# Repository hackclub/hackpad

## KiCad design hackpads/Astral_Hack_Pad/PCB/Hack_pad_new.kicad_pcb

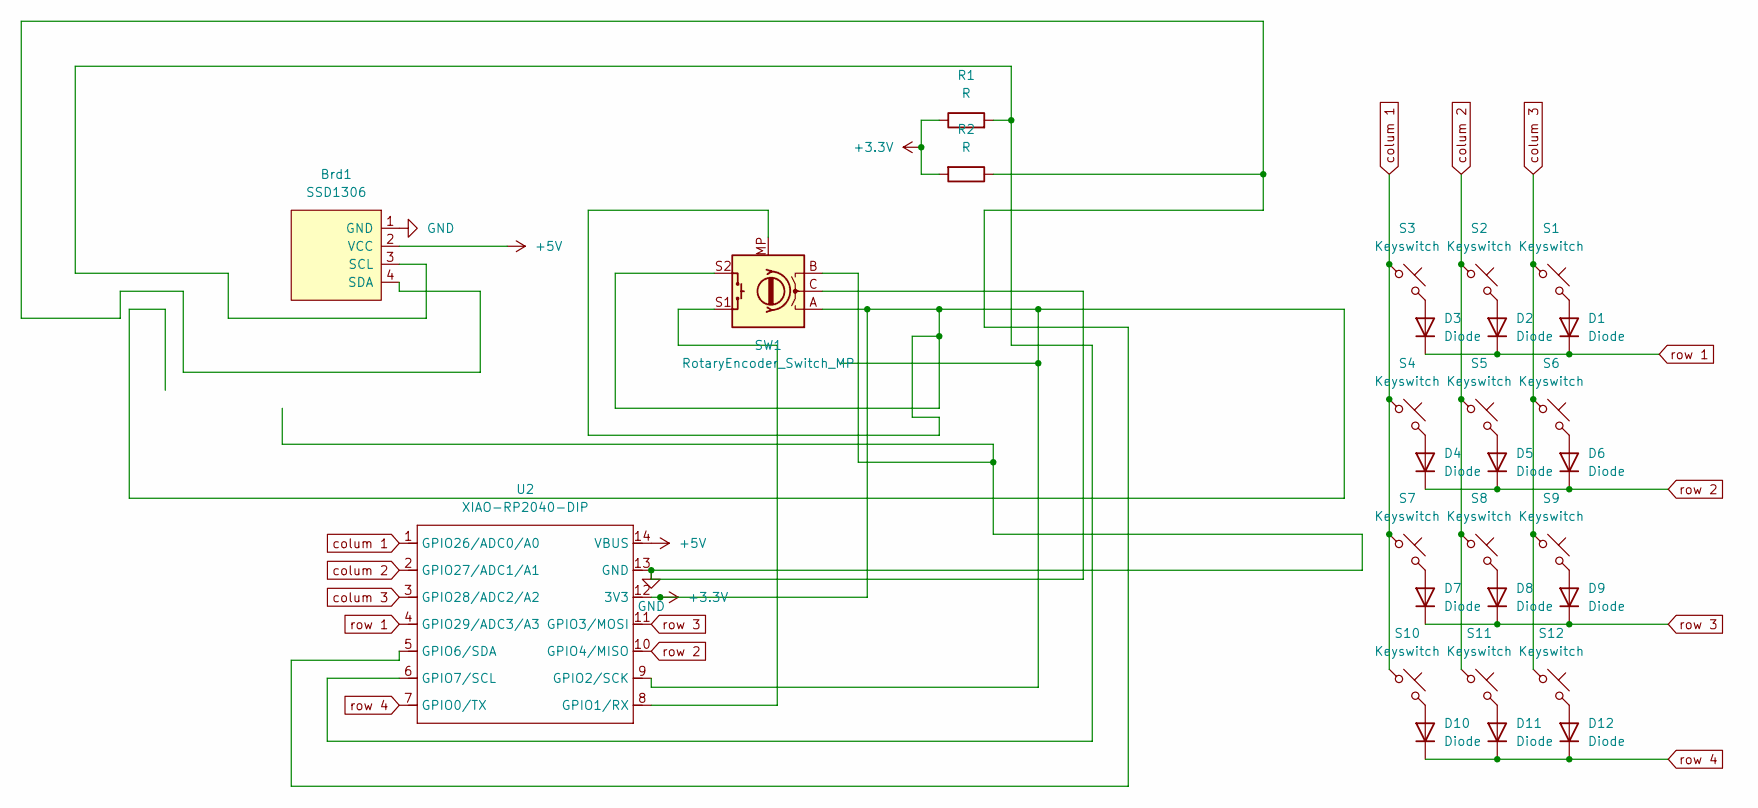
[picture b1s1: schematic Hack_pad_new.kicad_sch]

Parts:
Brd1: SSD1306; 128x64OLED
D1, D2, D3, D4, D5, D6, D7, D8, D9, D10, D11, D12: Diode; Diode_DO-35
R1, R2: R; R_Axial_DIN0204_L3.6mm_D1.6mm_P7.62mm_Horizontal
S1, S2, S3, S4, S5, S6, S7, S8, S9, S10, S11, S12: Keyswitch; MX_PCB_1.00u
SW1: RotaryEncoder_Switch_MP; Encoder_EC11_MX
U2: XIAO-RP2040-DIP

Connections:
+3.3V: R1.1, R2.2, SW1.A, SW1.MP, SW1.S2, U2.9 (GPIO2/SCK), U2.12 (3V3)
+5V: Brd1.2 (VCC), U2.14 (VBUS)
GND: Brd1.1 (GND), SW1.B, SW1.C, U2.13 (GND)
unnamed: Brd1.3 (SCL), R1.2, U2.6 (GPIO7/SCL)
unnamed: Brd1.4 (SDA), R2.1, U2.5 (GPIO6/SDA)
unnamed: D1.2 (A), S1.2
unnamed: D2.2 (A), S2.2
unnamed: D3.2 (A), S3.2
unnamed: D4.2 (A), S4.2
unnamed: D5.2 (A), S5.2
unnamed: D6.2 (A), S6.2
unnamed: D7.2 (A), S7.2
unnamed: D8.2 (A), S8.2
unnamed: D9.2 (A), S9.2
unnamed: D10.2 (A), S10.2
unnamed: D11.2 (A), S11.2
unnamed: D12.2 (A), S12.2
unnamed: SW1.S1, U2.8 (GPIO1/RX)
colum 1: S3.1, S4.1, S7.1, S10.1, U2.1 (GPIO26/ADC0/A0)
colum 2: S2.1, S5.1, S8.1, S11.1, U2.2 (GPIO27/ADC1/A1)
colum 3: S1.1, S6.1, S9.1, S12.1, U2.3 (GPIO28/ADC2/A2)
row 1: D1.1 (K), D2.1 (K), D3.1 (K), U2.4 (GPIO29/ADC3/A3)
row 2: D4.1 (K), D5.1 (K), D6.1 (K), U2.10 (GPIO4/MISO)
row 3: D7.1 (K), D8.1 (K), D9.1 (K), U2.11 (GPIO3/MOSI)
row 4: D10.1 (K), D11.1 (K), D12.1 (K), U2.7 (GPIO0/TX)

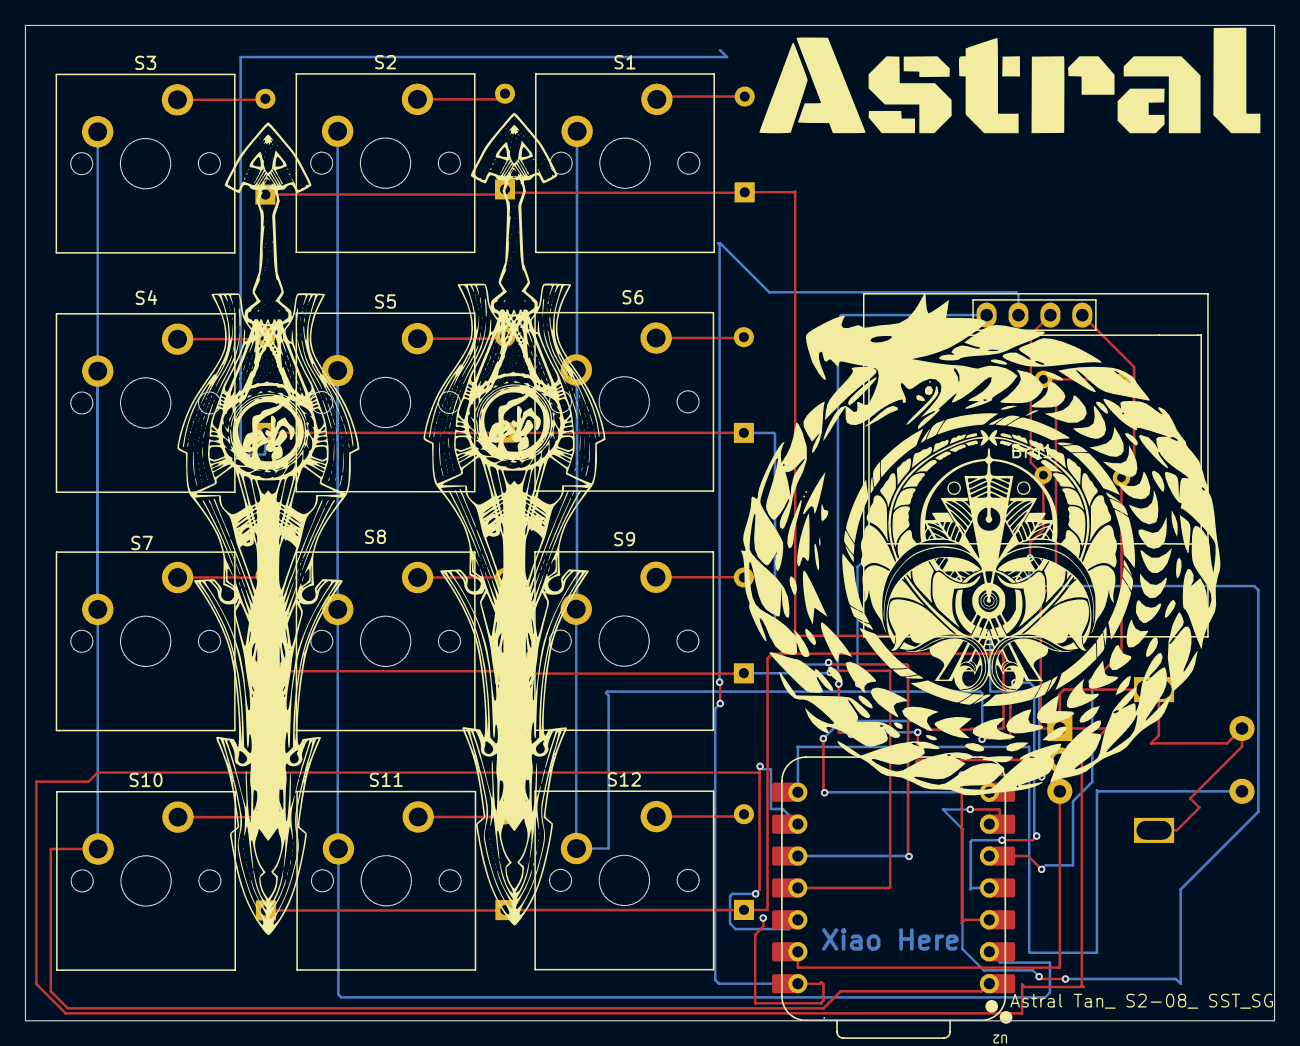
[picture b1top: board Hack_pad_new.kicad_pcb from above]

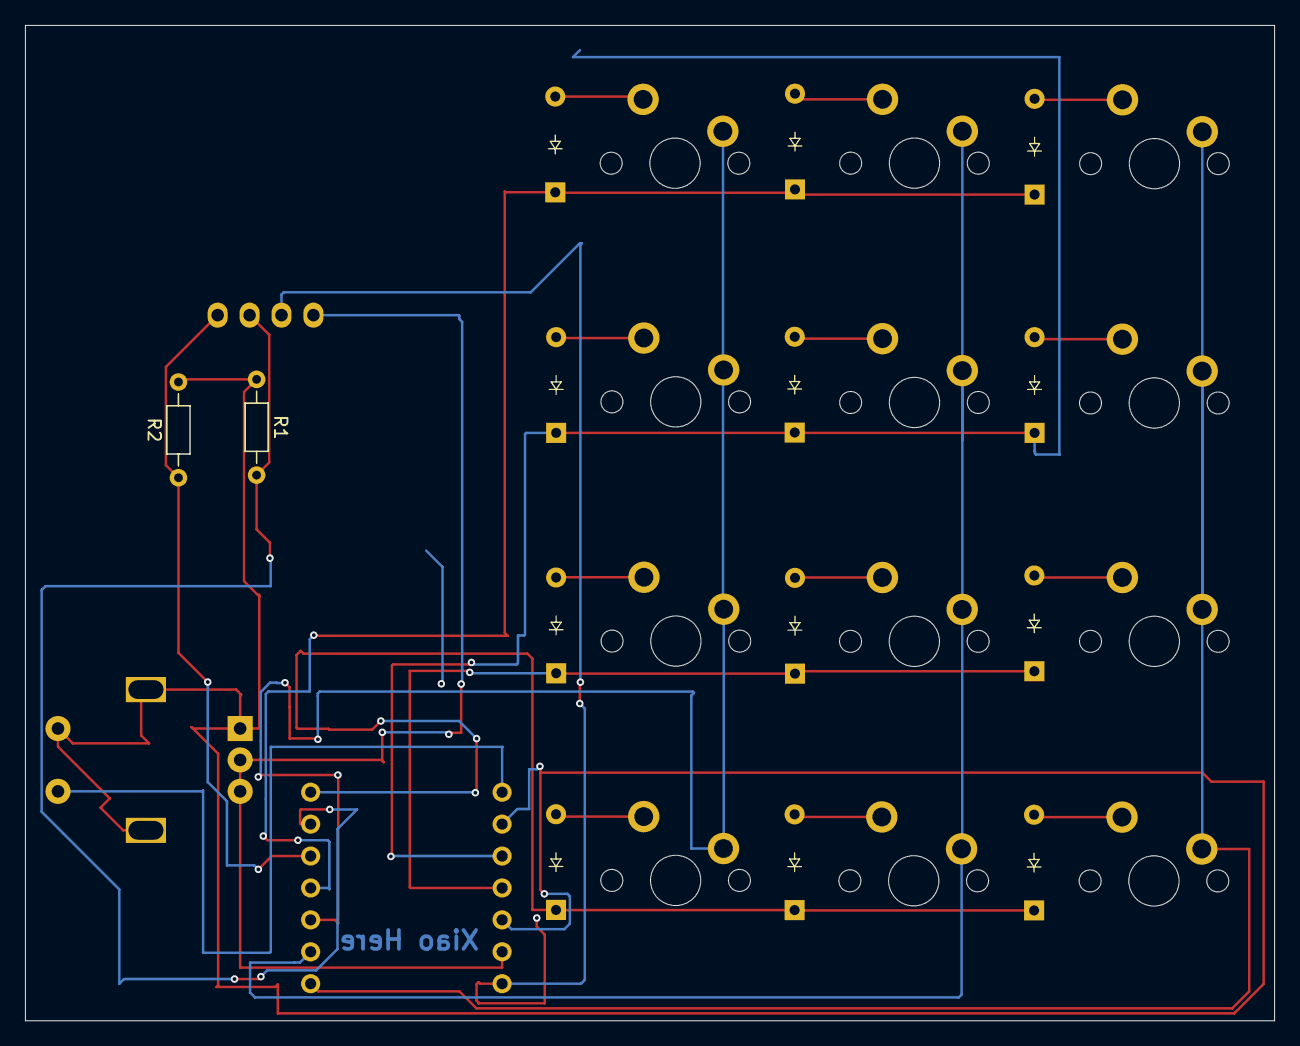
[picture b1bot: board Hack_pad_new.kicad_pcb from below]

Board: 2 copper layers, 99.4 x 79.2 mm, 29 parts (14 on the bottom side), 25 nets.

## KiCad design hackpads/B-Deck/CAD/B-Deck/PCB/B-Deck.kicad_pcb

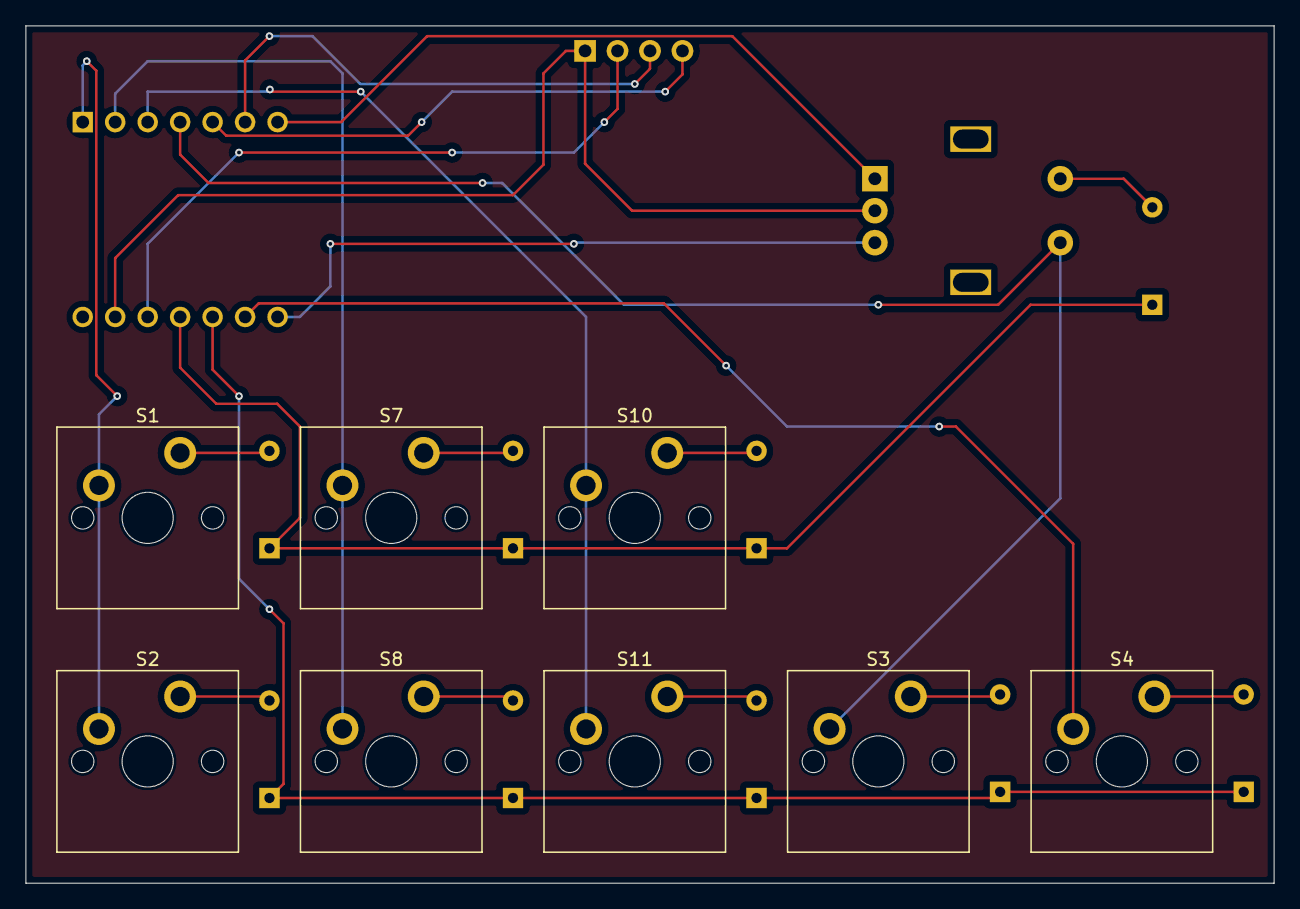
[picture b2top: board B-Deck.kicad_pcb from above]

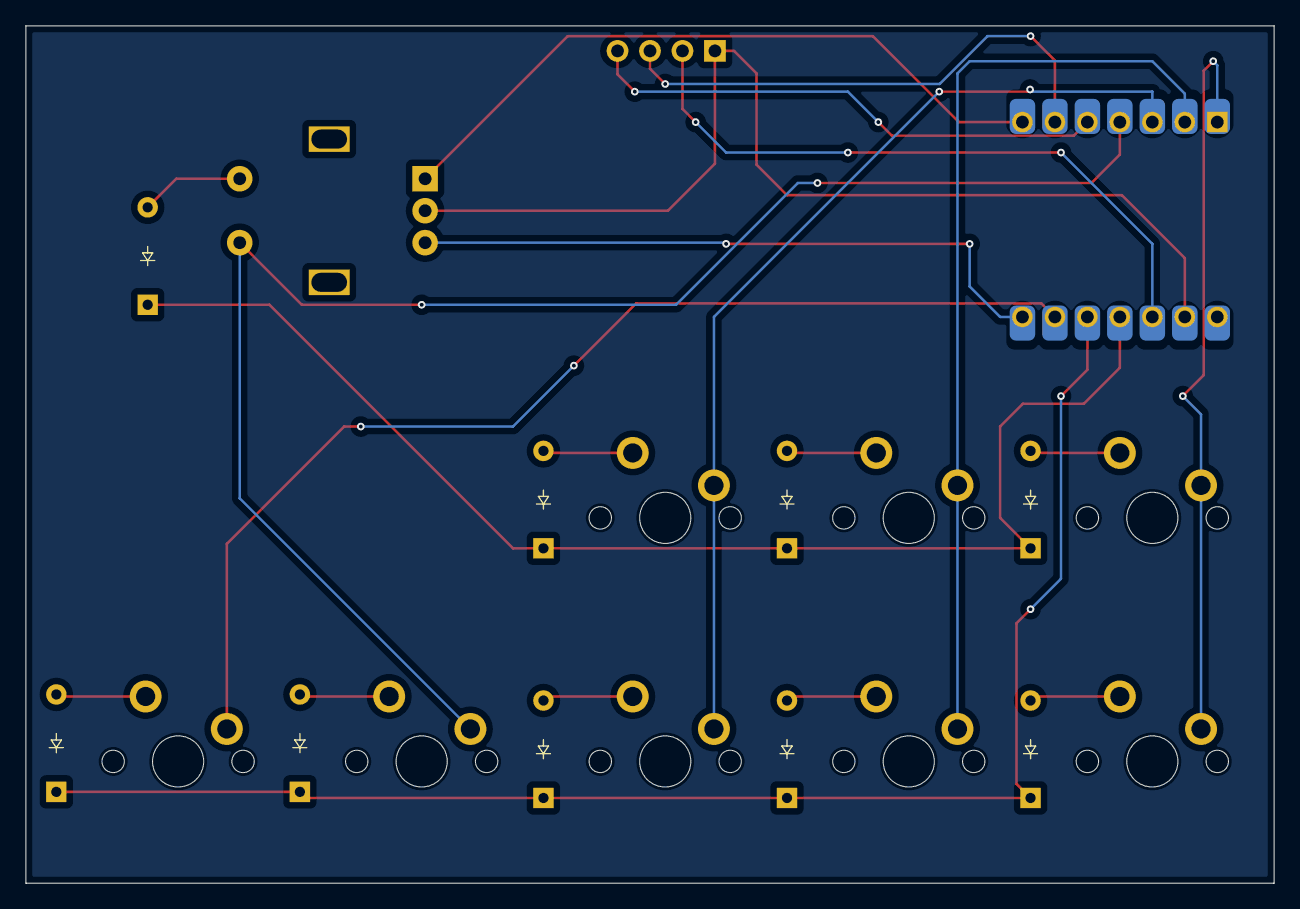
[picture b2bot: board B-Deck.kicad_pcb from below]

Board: 2 copper layers, 97.6 x 67.1 mm, 20 parts (10 on the bottom side), 22 nets.

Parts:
D1, D3, D4, D5, D6, D7, D8, D10, D11: Diode; Diode_DO-35
J1: OLED_128x64
S1, S2, S3, S4, S7, S8, S10, S11: Keyswitch; MX_PCB_1.00u
SW2: RotaryEncoder_Switch; Encoder_EC11_MX
U1: MCU_Seeed_XIAO_RP2040; Seeed_XIAO_RP2040

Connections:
Column 0: S1.1, S2.1, U1.1 (PA02_A0_D0)
Column 1: S7.1, S8.1, U1.2 (PA4_A1_D1)
Column 2: S10.1, S11.1, U1.3 (PA10_A2_D2)
Column 3: S3.1, SW2.S1, U1.4 (PA11_A3_D3)
Column 4: S4.1, U1.9 (PA7_A8_D8_SCK)
GND: J1.1 (GND), SW2.C, U1.13 (GND)
unnamed: D3.2 (A), S3.2
unnamed: D4.2 (A), S4.2
unnamed: D5.2 (A), S1.2
unnamed: D6.2 (A), S2.2
unnamed: D7.2 (A), S7.2
unnamed: D8.2 (A), S8.2
unnamed: D10.2 (A), S10.2
unnamed: D11.2 (A), S11.2
unnamed: J1.3 (SCL), U1.6 (PA9_A5_D5_SCL)
unnamed: J1.4 (SDA), U1.5 (PA8_A4_D4_SDA)
unnamed: J1.2 (VCC), U1.12 (3V3)
unnamed: SW2.A, U1.7 (PB08_A6_D6_TX)
unnamed: SW2.B, U1.8 (PB09_A7_D7_RX)
RE S2: D1.2 (A), SW2.S2
Row 0: D1.1 (K), D5.1 (K), D7.1 (K), D10.1 (K), U1.11 (PA6_A10_D10_MOSI)
Row 1: D3.1 (K), D4.1 (K), D6.1 (K), D8.1 (K), D11.1 (K), U1.10 (PA5_A9_D9_MISO)

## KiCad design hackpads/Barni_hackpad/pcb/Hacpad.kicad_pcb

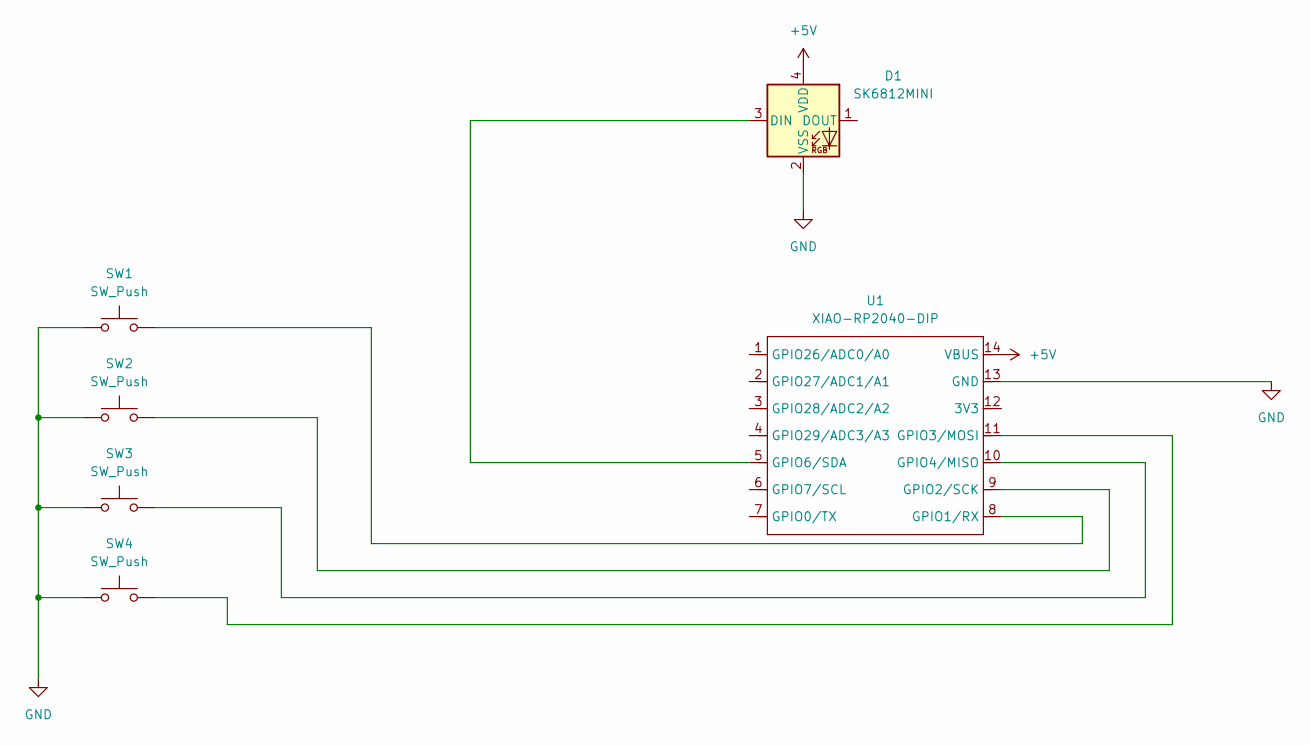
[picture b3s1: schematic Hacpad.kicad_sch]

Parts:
D1: SK6812MINI; LED_SK6812MINI_PLCC4_3.5x3.5mm_P1.75mm
SW1, SW2, SW3, SW4: SW_Push; SW_Cherry_MX_1.00u_PCB
U1: XIAO-RP2040-DIP

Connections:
+5V: D1.4 (VDD), U1.14 (VBUS)
GND: D1.2 (VSS), SW1.1, SW2.1, SW3.1, SW4.1, U1.13 (GND)
unnamed: D1.3 (DIN), U1.5 (GPIO6/SDA)
unnamed: SW1.2, U1.8 (GPIO1/RX)
unnamed: SW2.2, U1.9 (GPIO2/SCK)
unnamed: SW4.2, U1.11 (GPIO3/MOSI)
unnamed: SW3.2, U1.10 (GPIO4/MISO)

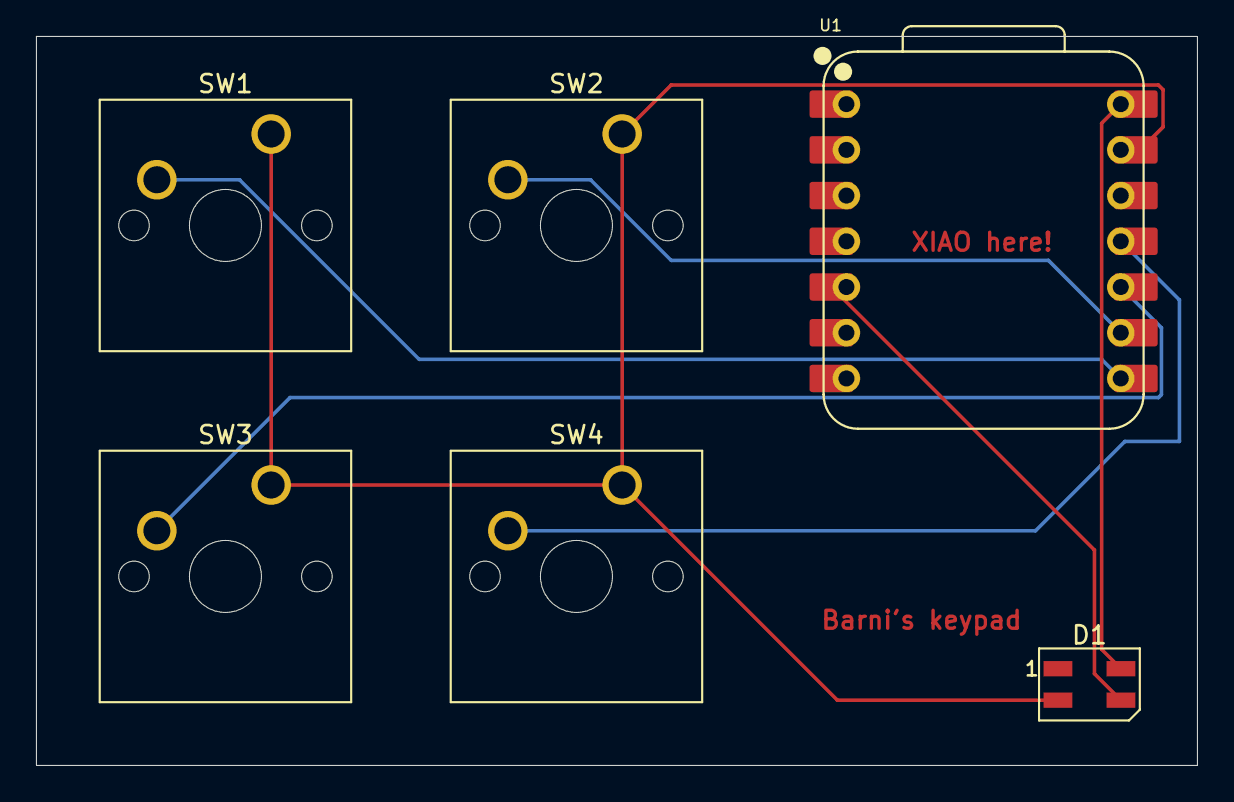
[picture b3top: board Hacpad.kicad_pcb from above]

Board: 2 copper layers, 64.5 x 40.5 mm, 6 parts (0 on the bottom side), 7 nets.

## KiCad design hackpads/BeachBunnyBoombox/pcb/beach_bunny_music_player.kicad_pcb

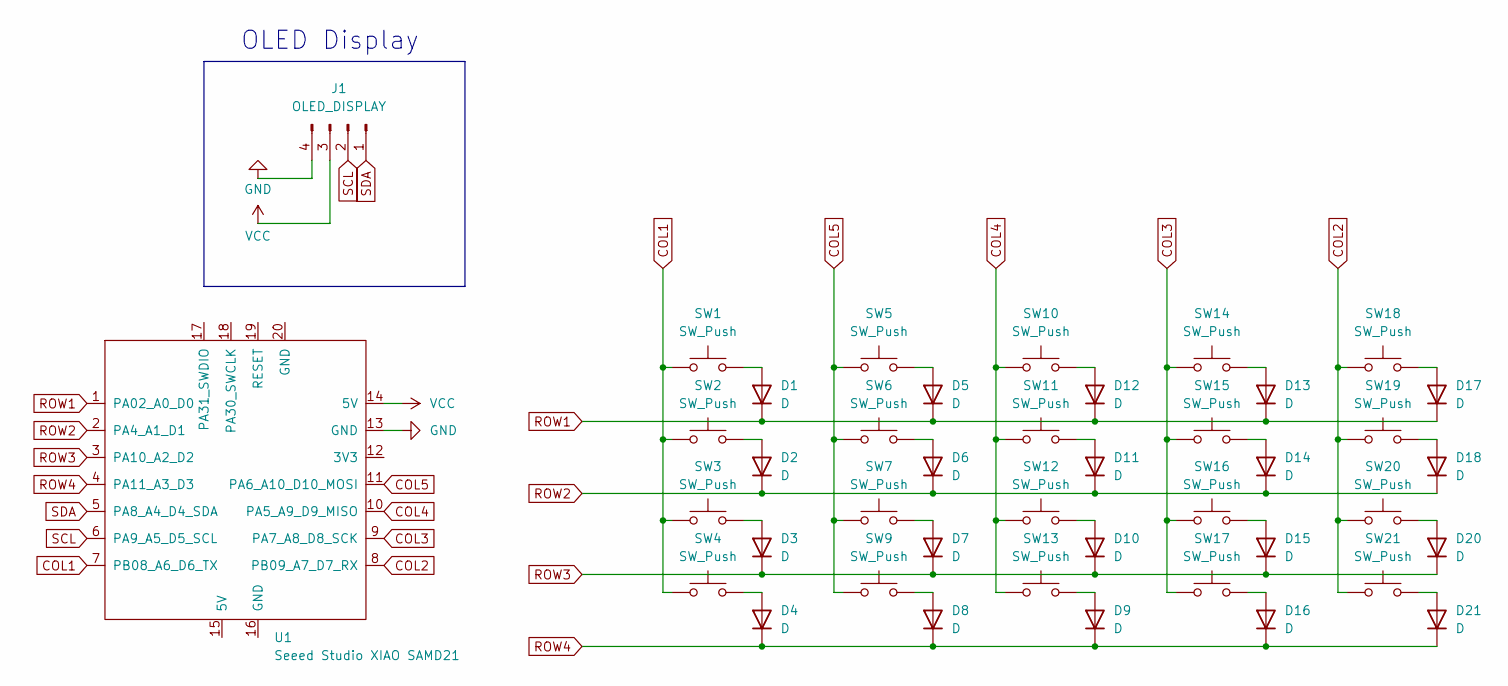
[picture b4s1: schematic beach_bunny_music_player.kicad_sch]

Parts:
D1, D2, D3, D4, D5, D6, D7, D8, D9, D10, D11, D12, D13, D14, D15, D16, D17, D18, D20, D21: D; D_DO-35_SOD27_P7.62mm_Horizontal
J1: OLED_DISPLAY; PinHeader_1x04_P2.54mm_Vertical
SW1, SW2, SW3, SW4, SW5, SW6, SW7, SW9, SW10, SW11, SW12, SW13, SW14, SW15, SW16, SW17, SW18, SW19, SW20, SW21: SW_Push; SW_Cherry_MX_1.00u_PCB
U1: Seeed Studio XIAO SAMD21; XIAO-Generic-Thruhole-14P-2.54-21X17.8MM

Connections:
COL1: SW1.1, SW2.1, SW3.1, SW4.1, U1.7 (PB08_A6_D6_TX)
COL2: SW18.1, SW19.1, SW20.1, SW21.1, U1.8 (PB09_A7_D7_RX)
COL3: SW14.1, SW15.1, SW16.1, SW17.1, U1.9 (PA7_A8_D8_SCK)
COL4: SW10.1, SW11.1, SW12.1, SW13.1, U1.10 (PA5_A9_D9_MISO)
COL5: SW5.1, SW6.1, SW7.1, SW9.1, U1.11 (PA6_A10_D10_MOSI)
GND: J1.4, U1.13 (GND)
unnamed: D1.2 (A), SW1.2
unnamed: D2.2 (A), SW2.2
unnamed: D3.2 (A), SW3.2
unnamed: D4.2 (A), SW4.2
unnamed: D5.2 (A), SW5.2
unnamed: D6.2 (A), SW6.2
unnamed: D7.2 (A), SW7.2
unnamed: D8.2 (A), SW9.2
unnamed: D9.2 (A), SW13.2
unnamed: D10.2 (A), SW12.2
unnamed: D11.2 (A), SW11.2
unnamed: D12.2 (A), SW10.2
unnamed: D13.2 (A), SW14.2
unnamed: D14.2 (A), SW15.2
unnamed: D15.2 (A), SW16.2
unnamed: D16.2 (A), SW17.2
unnamed: D17.2 (A), SW18.2
unnamed: D18.2 (A), SW19.2
unnamed: D20.2 (A), SW20.2
unnamed: D21.2 (A), SW21.2
ROW1: D1.1 (K), D5.1 (K), D12.1 (K), D13.1 (K), D17.1 (K), U1.1 (PA02_A0_D0)
ROW2: D2.1 (K), D6.1 (K), D11.1 (K), D14.1 (K), D18.1 (K), U1.2 (PA4_A1_D1)
ROW3: D3.1 (K), D7.1 (K), D10.1 (K), D15.1 (K), D20.1 (K), U1.3 (PA10_A2_D2)
ROW4: D4.1 (K), D8.1 (K), D9.1 (K), D16.1 (K), D21.1 (K), U1.4 (PA11_A3_D3)
SCL: J1.2, U1.6 (PA9_A5_D5_SCL)
SDA: J1.1, U1.5 (PA8_A4_D4_SDA)
VCC: J1.3, U1.14 (5V)

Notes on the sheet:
OLED Display

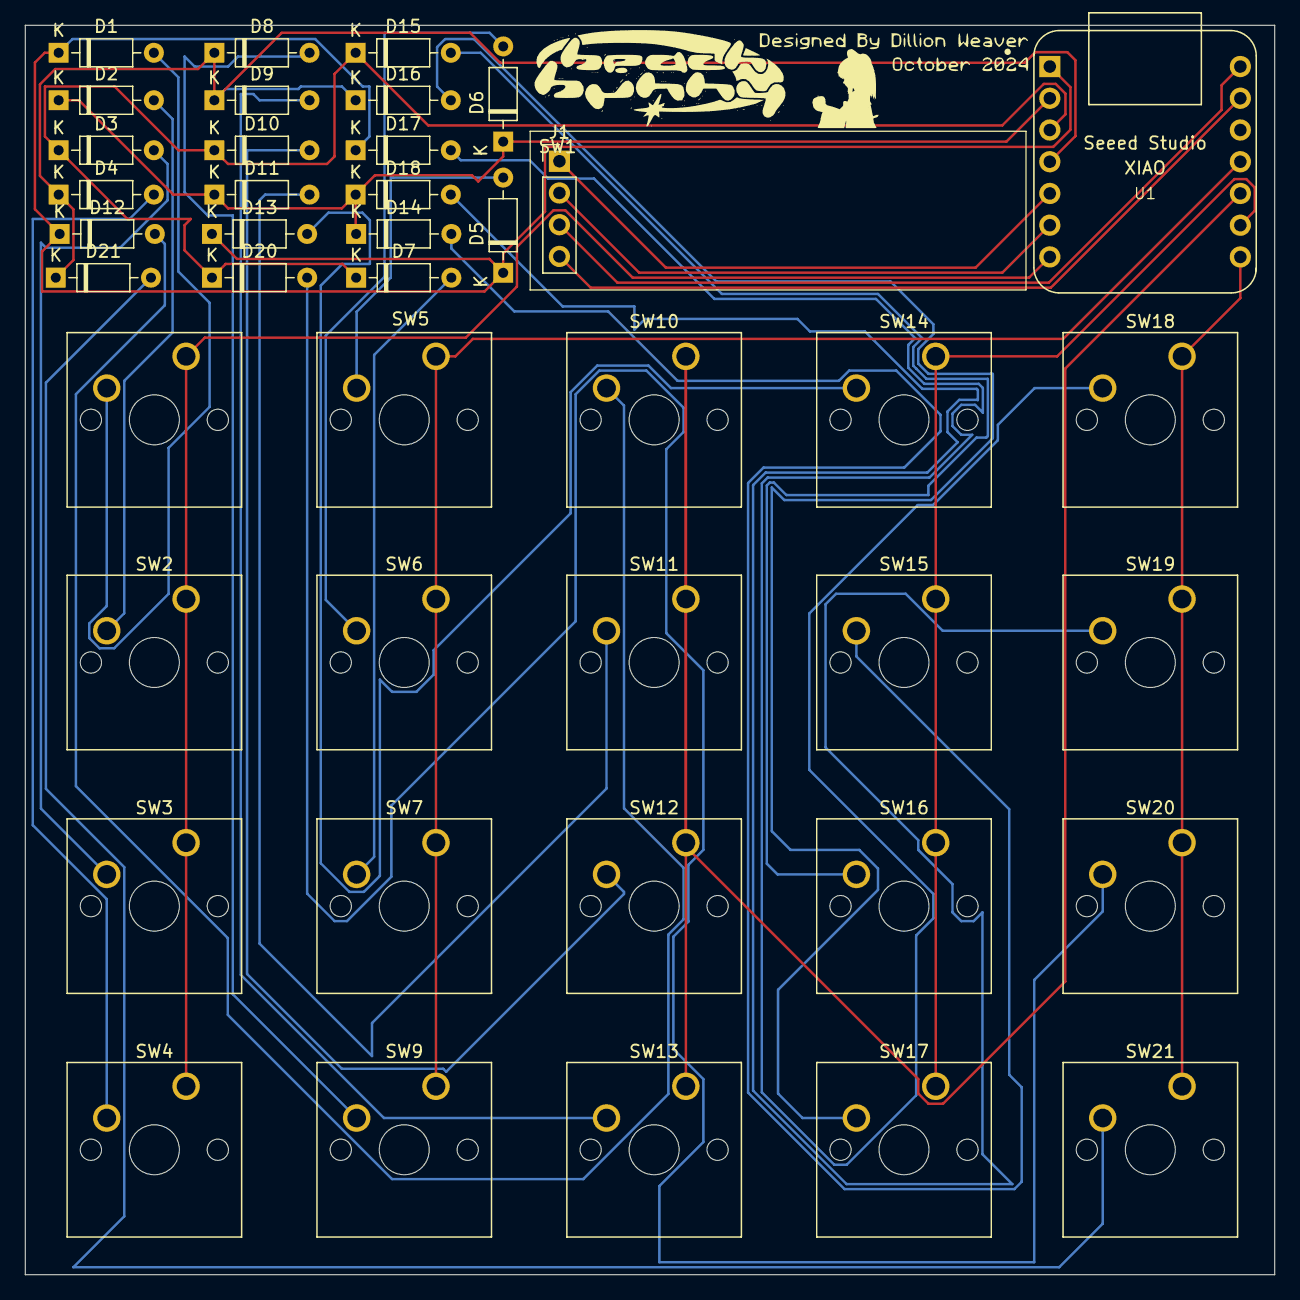
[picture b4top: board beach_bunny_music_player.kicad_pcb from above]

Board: 2 copper layers, 100.0 x 100.0 mm, 42 parts (0 on the bottom side), 33 nets.

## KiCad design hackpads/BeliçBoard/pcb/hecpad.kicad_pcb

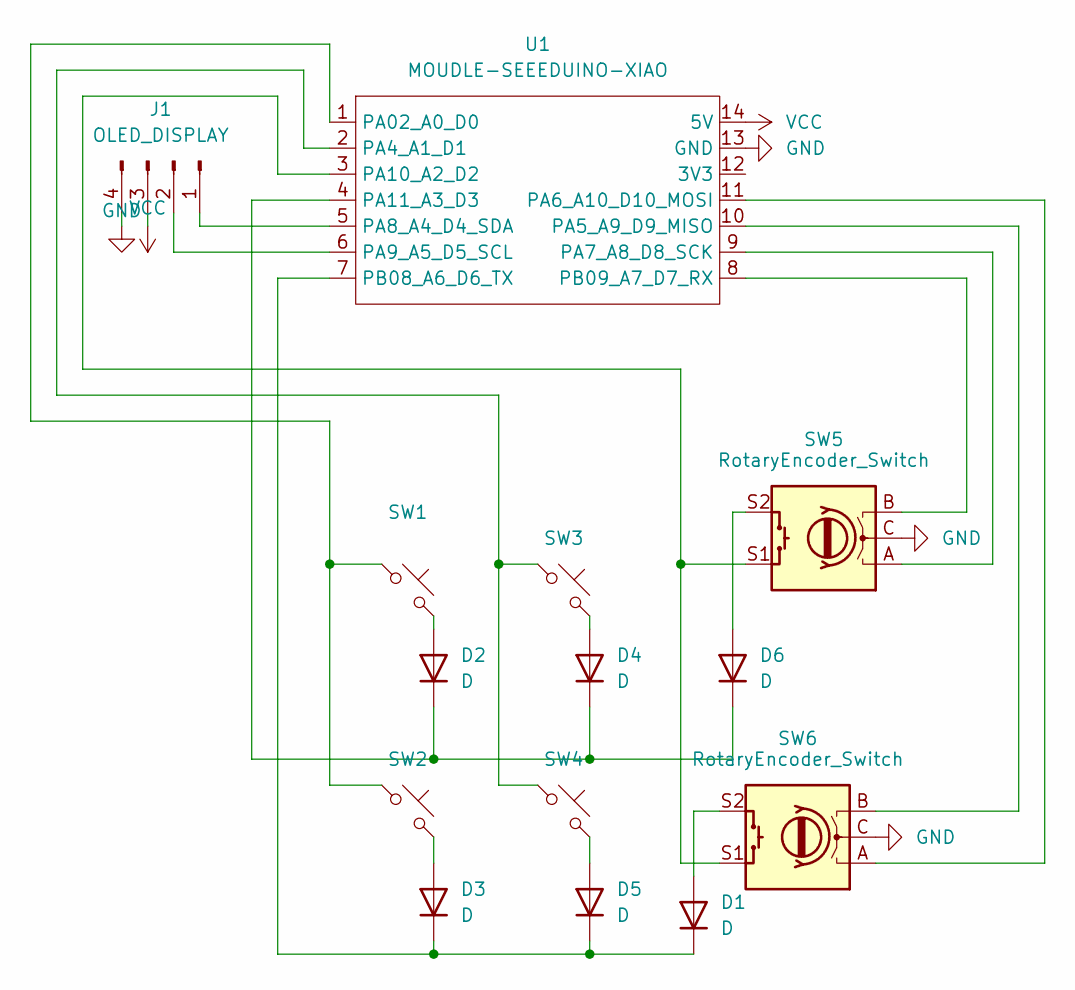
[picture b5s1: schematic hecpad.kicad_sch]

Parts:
D1, D2, D3, D4, D5, D6: D; D_DO-35_SOD27_P7.62mm_Horizontal
J1: OLED_DISPLAY; SSD1306-0.91-OLED-4pin-128x32
SW1, SW2, SW3, SW4: SW_Push_45deg; SW_Cherry_MX_1.00u_PCB
SW5, SW6: RotaryEncoder_Switch; RotaryEncoder_Alps_EC11E-Switch_Vertical_H20mm
U1: MOUDLE-SEEEDUINO-XIAO; XIAO-Generic-Hybrid-14P-2.54-21X17.8MM

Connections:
GND: J1.4, SW5.C, SW6.C, U1.13 (GND)
unnamed: D1.2 (A), SW6.S2
unnamed: D1.1 (K), D3.1 (K), D5.1 (K), U1.7 (PB08_A6_D6_TX)
unnamed: D2.2 (A), SW1.2
unnamed: D2.1 (K), D4.1 (K), D6.1 (K), U1.4 (PA11_A3_D3)
unnamed: D3.2 (A), SW2.2
unnamed: D4.2 (A), SW3.2
unnamed: D5.2 (A), SW4.2
unnamed: D6.2 (A), SW5.S2
unnamed: J1.1, U1.5 (PA8_A4_D4_SDA)
unnamed: J1.2, U1.6 (PA9_A5_D5_SCL)
unnamed: SW1.1, SW2.1, U1.1 (PA02_A0_D0)
unnamed: SW3.1, SW4.1, U1.2 (PA4_A1_D1)
unnamed: SW6.B, U1.10 (PA5_A9_D9_MISO)
unnamed: SW6.A, U1.11 (PA6_A10_D10_MOSI)
unnamed: SW5.A, U1.9 (PA7_A8_D8_SCK)
unnamed: SW5.S1, SW6.S1, U1.3 (PA10_A2_D2)
unnamed: SW5.B, U1.8 (PB09_A7_D7_RX)
VCC: J1.3, U1.14 (5V)

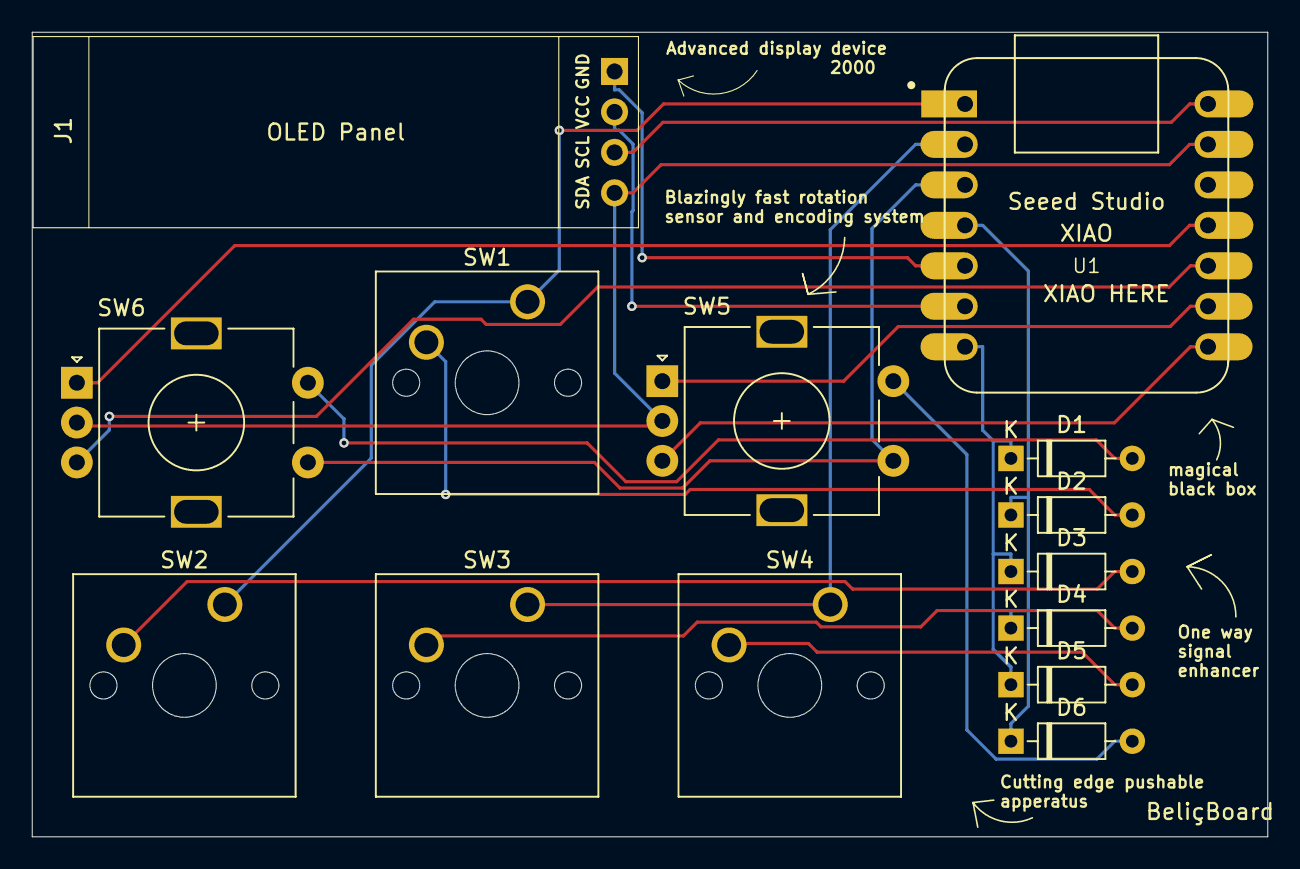
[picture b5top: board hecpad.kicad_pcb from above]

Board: 2 copper layers, 77.5 x 50.5 mm, 14 parts (0 on the bottom side), 19 nets.

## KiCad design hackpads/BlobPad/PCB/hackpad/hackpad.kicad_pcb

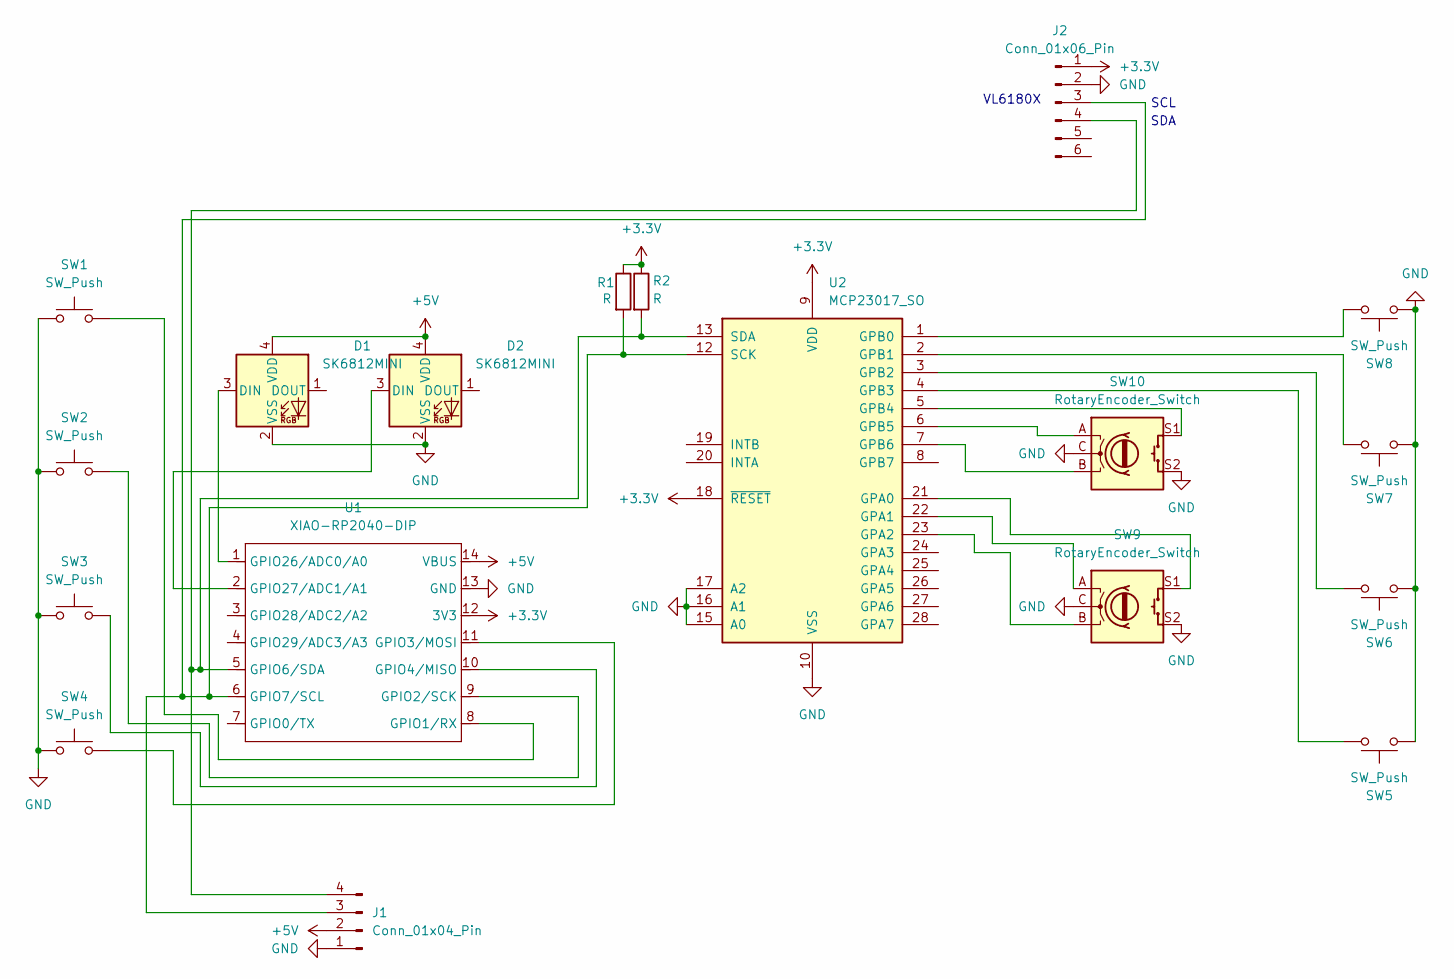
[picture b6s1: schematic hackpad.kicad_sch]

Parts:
D1, D2: SK6812MINI; LED_SK6812MINI_PLCC4_3.5x3.5mm_P1.75mm
J1: Conn_01x04_Pin; 128x64OLED
J2: Conn_01x06_Pin; PinHeader_1x06_P2.54mm_Vertical
R1, R2: R; R_Axial_DIN0204_L3.6mm_D1.6mm_P7.62mm_Horizontal
SW1, SW2, SW3, SW4, SW5, SW6, SW7, SW8: SW_Push; SW_Cherry_MX_1.00u_PCB
SW9, SW10: RotaryEncoder_Switch; RotaryEncoder_Alps_EC11E-Switch_Vertical_H20mm_CircularMoun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
U1: XIAO-RP2040-DIP
U2: MCP23017_SO; SOIC-28W_7.5x17.9mm_P1.27mm

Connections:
+3.3V: J2.1, R1.1, R2.1, U1.12 (3V3), U2.9 (VDD), U2.18 (~RESET)
+5V: D1.4 (VDD), D2.4 (VDD), J1.2, U1.14 (VBUS)
GND: D1.2 (VSS), D2.2 (VSS), J1.1, J2.2, SW1.1, SW2.1, SW3.1, SW4.1, SW5.1, SW6.1, SW7.1, SW8.1, SW9.C, SW9.S2, SW10.C, SW10.S2, U1.13 (GND), U2.10 (VSS), U2.15 (A0), U2.16 (A1), U2.17 (A2)
unnamed: D1.3 (DIN), U1.1 (GPIO26/ADC0/A0)
unnamed: D2.3 (DIN), U1.2 (GPIO27/ADC1/A1)
unnamed: J1.3, J2.3, R1.2, U1.6 (GPIO7/SCL), U2.12 (SCK)
unnamed: J1.4, J2.4, R2.2, U1.5 (GPIO6/SDA), U2.13 (SDA)
unnamed: SW1.2, U1.8 (GPIO1/RX)
unnamed: SW2.2, U1.9 (GPIO2/SCK)
unnamed: SW4.2, U1.11 (GPIO3/MOSI)
unnamed: SW3.2, U1.10 (GPIO4/MISO)
unnamed: SW9.S1, U2.21 (GPA0)
unnamed: SW9.A, U2.22 (GPA1)
unnamed: SW9.B, U2.23 (GPA2)
unnamed: SW8.2, U2.1 (GPB0)
unnamed: SW7.2, U2.2 (GPB1)
unnamed: SW6.2, U2.3 (GPB2)
unnamed: SW5.2, U2.4 (GPB3)
unnamed: SW10.S1, U2.5 (GPB4)
unnamed: SW10.A, U2.6 (GPB5)
unnamed: SW10.B, U2.7 (GPB6)

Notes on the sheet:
SDA
SCL
VL6180X

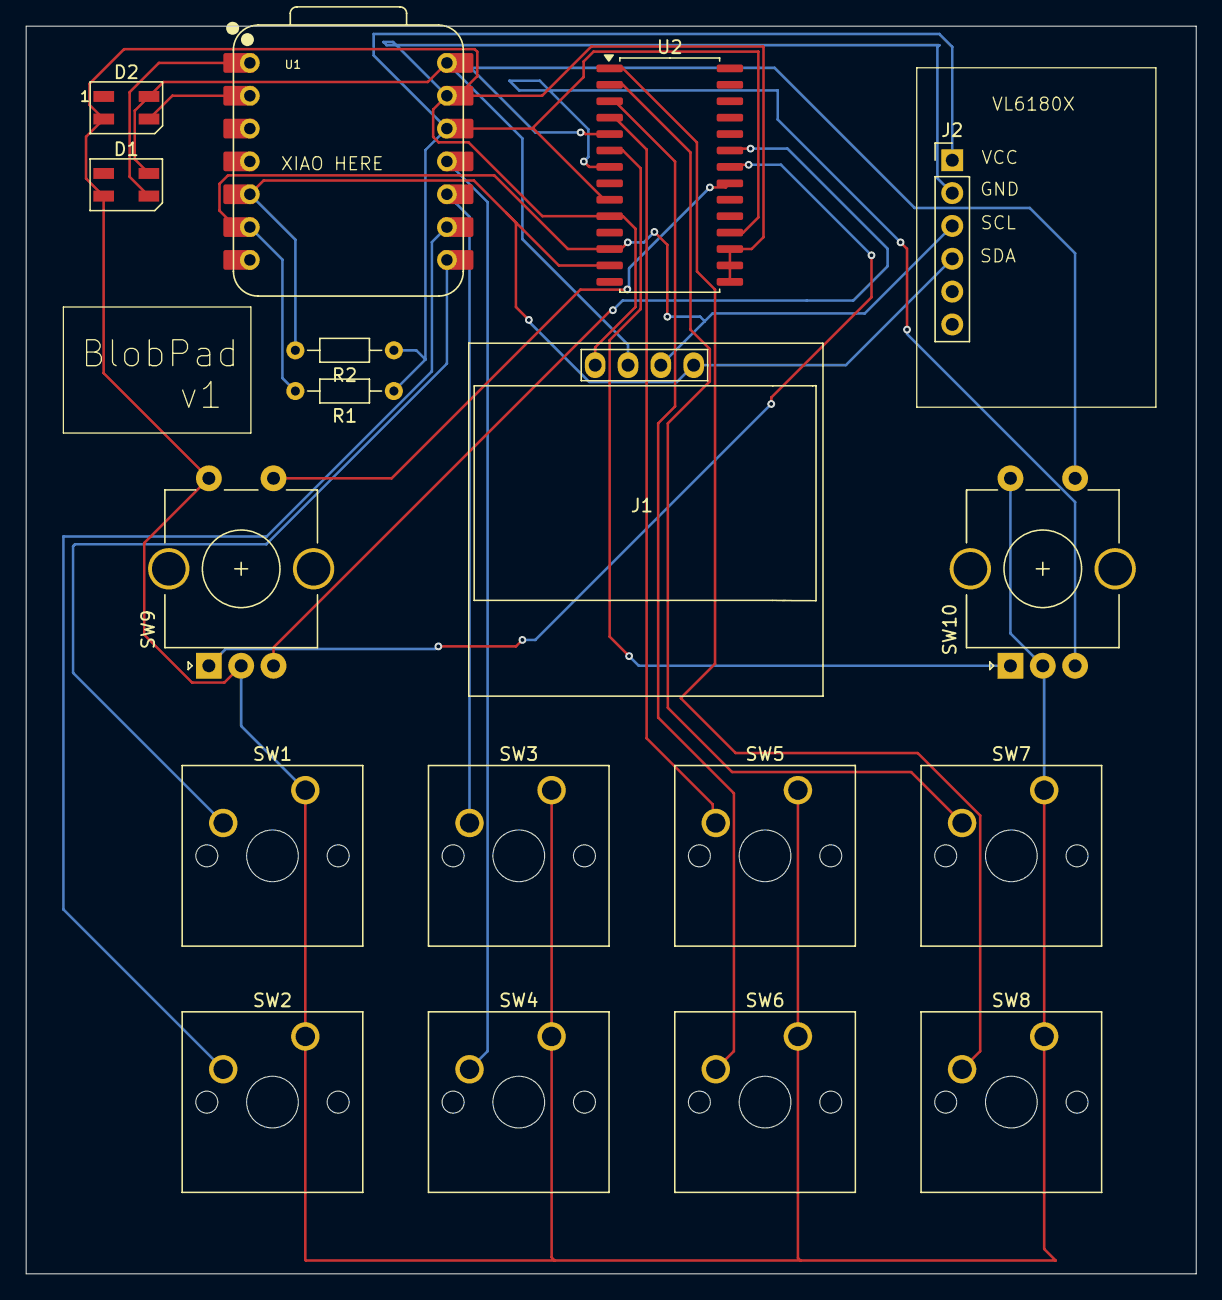
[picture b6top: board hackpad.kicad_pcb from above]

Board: 2 copper layers, 90.5 x 96.5 mm, 18 parts (0 on the bottom side), 21 nets.
